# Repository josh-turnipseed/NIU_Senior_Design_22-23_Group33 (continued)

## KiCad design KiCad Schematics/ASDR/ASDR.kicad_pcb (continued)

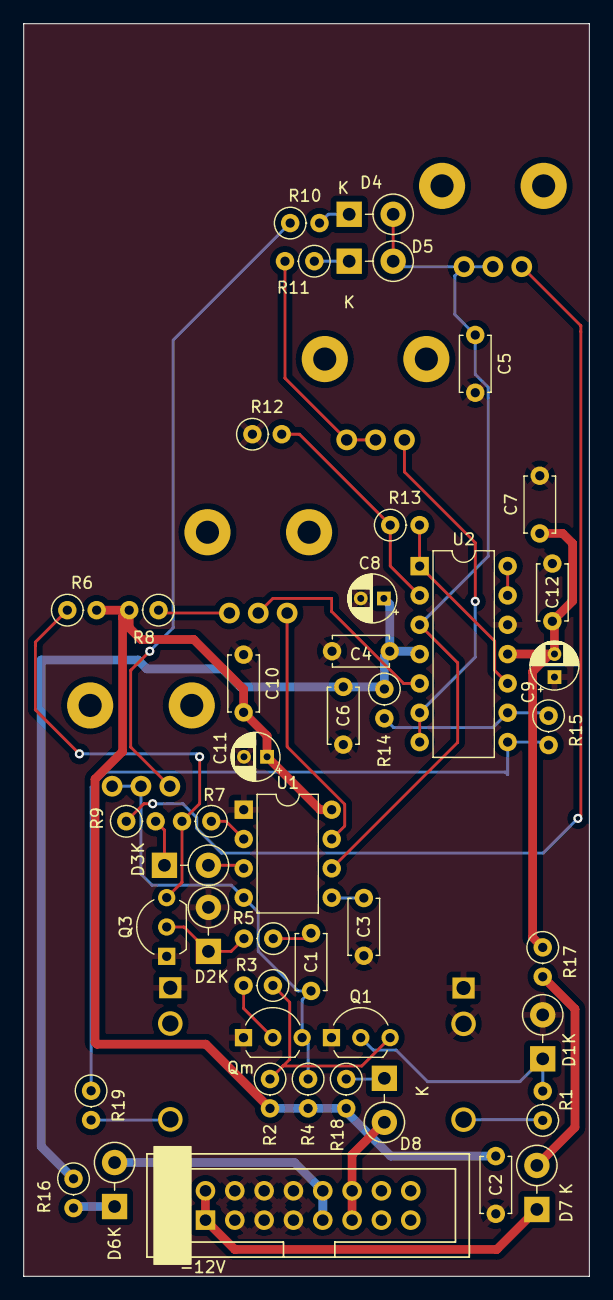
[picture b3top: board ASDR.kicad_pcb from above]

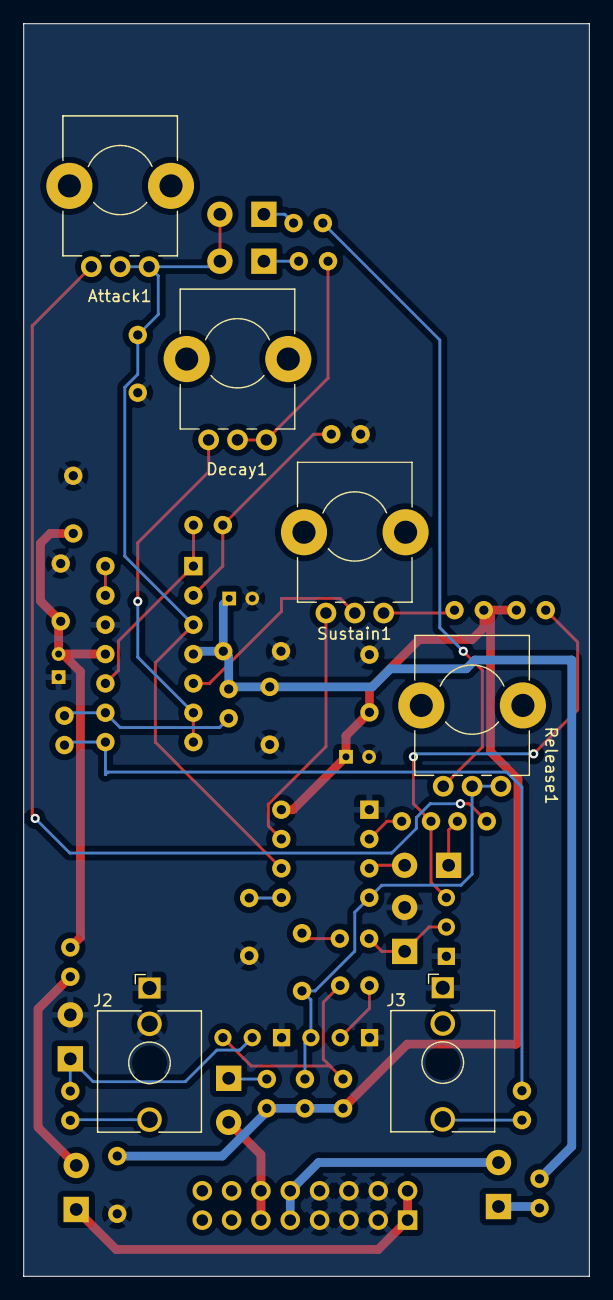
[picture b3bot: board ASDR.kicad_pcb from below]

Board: 2 copper layers, 49.0 x 108.5 mm, 51 parts (6 on the bottom side), 38 nets.

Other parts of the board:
Qm: 2N3904; TO-92L_Inline_Wide

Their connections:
GND: Qm.1 (E); also elsewhere on the board
unnamed 6: Qm.3 (C); also elsewhere on the board
unnamed 26: Qm.2 (B); also elsewhere on the board

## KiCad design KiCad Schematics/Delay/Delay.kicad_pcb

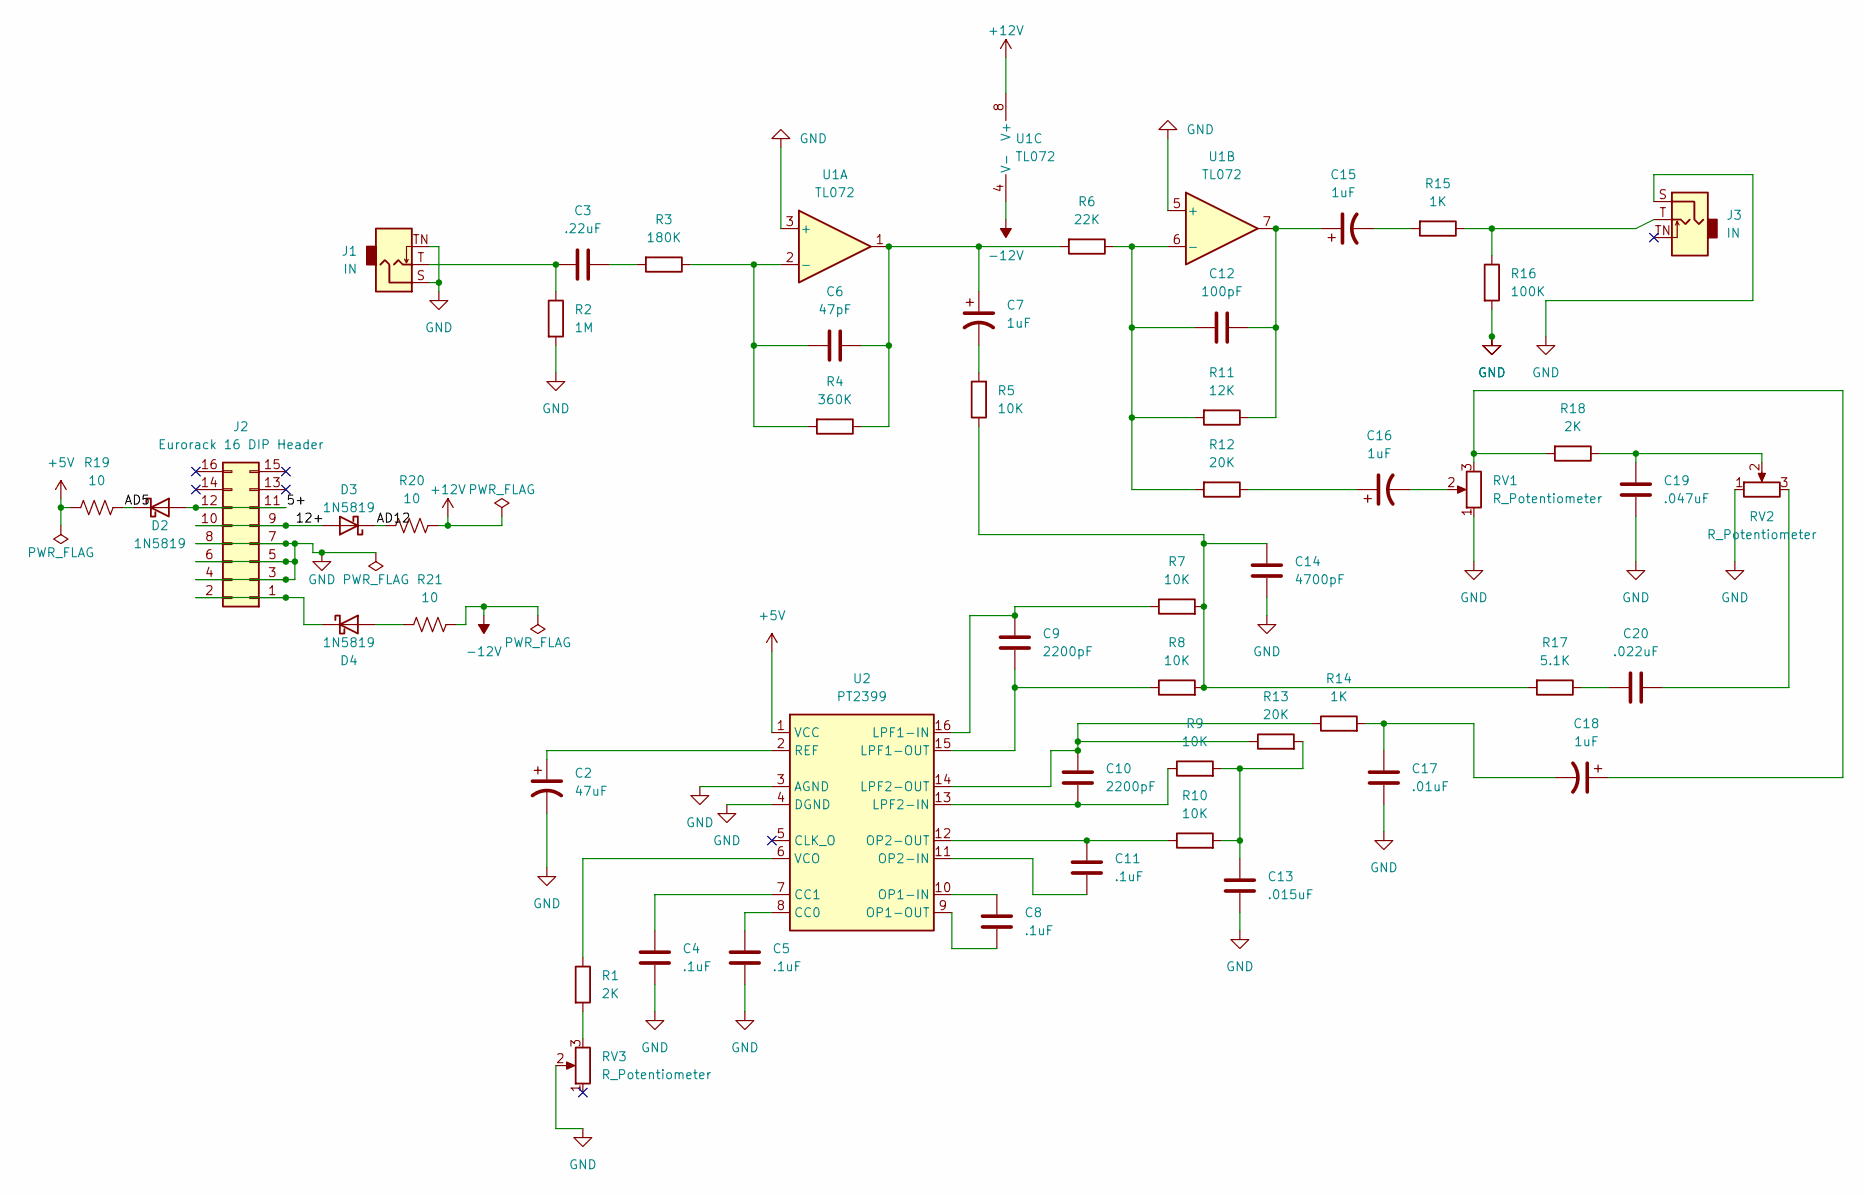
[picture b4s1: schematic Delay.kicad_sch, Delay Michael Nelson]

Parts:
C2: 47uF; CP_Radial_D5.0mm_P2.00mm
C3: .22uF; C_Disc_D3.8mm_W2.6mm_P2.50mm
C4, C5, C8, C11: .1uF; C_Disc_D3.8mm_W2.6mm_P2.50mm
C6: 47pF; C_Disc_D3.8mm_W2.6mm_P2.50mm
C7, C15, C16, C18: 1uF; CP_Radial_D5.0mm_P2.00mm
C9, C10: 2200pF; C_Disc_D3.8mm_W2.6mm_P2.50mm
C12: 100pF; C_Disc_D3.8mm_W2.6mm_P2.50mm
C13: .015uF; C_Disc_D3.8mm_W2.6mm_P2.50mm
C14: 4700pF; C_Disc_D3.8mm_W2.6mm_P2.50mm
C17: .01uF; C_Disc_D3.8mm_W2.6mm_P2.50mm
C19: .047uF; C_Disc_D3.8mm_W2.6mm_P2.50mm
C20: .022uF; C_Disc_D3.8mm_W2.6mm_P2.50mm
D2, D3, D4: 1N5819; D_DO-41_SOD81_P10.16mm_Horizontal
J1, J3: IN; Jack_3.5mm_QingPu_WQP-PJ398SM_Vertical_CircularHoles
J2: Eurorack 16 DIP Header; Eurorack_16_pin_header
R1, R18: 2K; R_Axial_DIN0207_L6.3mm_D2.5mm_P7.62mm_Horizontal
R2: 1M; R_Axial_DIN0207_L6.3mm_D2.5mm_P7.62mm_Horizontal
R3: 180K; R_Axial_DIN0207_L6.3mm_D2.5mm_P7.62mm_Horizontal
R4: 360K; R_Axial_DIN0207_L6.3mm_D2.5mm_P7.62mm_Horizontal
R5, R7, R8, R9, R10: 10K; R_Axial_DIN0207_L6.3mm_D2.5mm_P7.62mm_Horizontal
R6: 22K; R_Axial_DIN0207_L6.3mm_D2.5mm_P7.62mm_Horizontal
R11: 12K; R_Axial_DIN0207_L6.3mm_D2.5mm_P7.62mm_Horizontal
R12, R13: 20K; R_Axial_DIN0207_L6.3mm_D2.5mm_P7.62mm_Horizontal
R14, R15: 1K; R_Axial_DIN0207_L6.3mm_D2.5mm_P7.62mm_Horizontal
R16: 100K; R_Axial_DIN0207_L6.3mm_D2.5mm_P7.62mm_Horizontal
R17: 5.1K; R_Axial_DIN0207_L6.3mm_D2.5mm_P7.62mm_Horizontal
R19, R20, R21: 10; R_Axial_DIN0207_L6.3mm_D2.5mm_P7.62mm_Horizontal
RV1, RV2, RV3: R_Potentiometer; Alpha_9mm_Potentiometer
U1: TL072; DIP-8_W7.62mm
U2: PT2399; DIP-16_W7.62mm

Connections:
+5V: R19.2, U2.1 (VCC)
+12V: R20.1, U1.8 (V+)
-12V: R21.1, U1.4 (V-)
/5+: D2.2 (A), J2.11, J2.12
/12+: D3.2 (A), J2.9, J2.10
/AD5: D2.1 (K), R19.1
/AD12: D3.1 (K), R20.2
GND: C2.2, C4.2, C5.2, C13.2, C14.2, C17.2, C19.1, J1.S, J1.TN, J2.3, J2.4, J2.5, J2.6, J2.7, J2.8, J3.S, R2.2, R16.2, RV1.1, RV2.1, RV3.2, U1.3 (+), U1.5 (+), U2.3 (AGND), U2.4 (DGND)
unnamed: C2.1, U2.2 (REF)
unnamed: C3.1, J1.T, R2.1
unnamed: C3.2, R3.2
unnamed: C4.1, U2.7 (CC1)
unnamed: C5.1, U2.8 (CC0)
unnamed: C6.1, R3.1, R4.2, U1.2 (-)
unnamed: C6.2, C7.1, R4.1, R6.2, U1.1
unnamed: C7.2, R5.2
unnamed: C8.1, U2.10 (OP1-IN)
unnamed: C8.2, U2.9 (OP1-OUT)
unnamed: C9.1, R7.1, U2.16 (LPF1-IN)
unnamed: C9.2, R8.1, U2.15 (LPF1-OUT)
unnamed: C10.1, R13.1, R14.1, U2.14 (LPF2-OUT)
unnamed: C10.2, R9.1, U2.13 (LPF2-IN)
unnamed: C11.1, R10.1, U2.12 (OP2-OUT)
unnamed: C11.2, U2.11 (OP2-IN)
unnamed: C12.1, R6.1, R11.2, R12.2, U1.6 (-)
unnamed: C12.2, C15.1, R11.1, U1.7
unnamed: C13.1, R9.2, R10.2, R13.2
unnamed: C14.1, R5.1, R7.2, R8.2, R17.2
unnamed: C15.2, R15.2
unnamed: C16.1, R12.1
unnamed: C16.2, RV1.2
unnamed: C17.1, C18.2, R14.2
unnamed: C18.1, R18.2, RV1.3
unnamed: C19.2, R18.1, RV2.2
unnamed: C20.1, RV2.3
unnamed: C20.2, R17.1
unnamed: D4.1 (K), J2.1, J2.2
unnamed: D4.2 (A), R21.2
unnamed: J3.T, R15.1, R16.1
unnamed: R1.1, U2.6 (VCO)
unnamed: R1.2, RV3.3

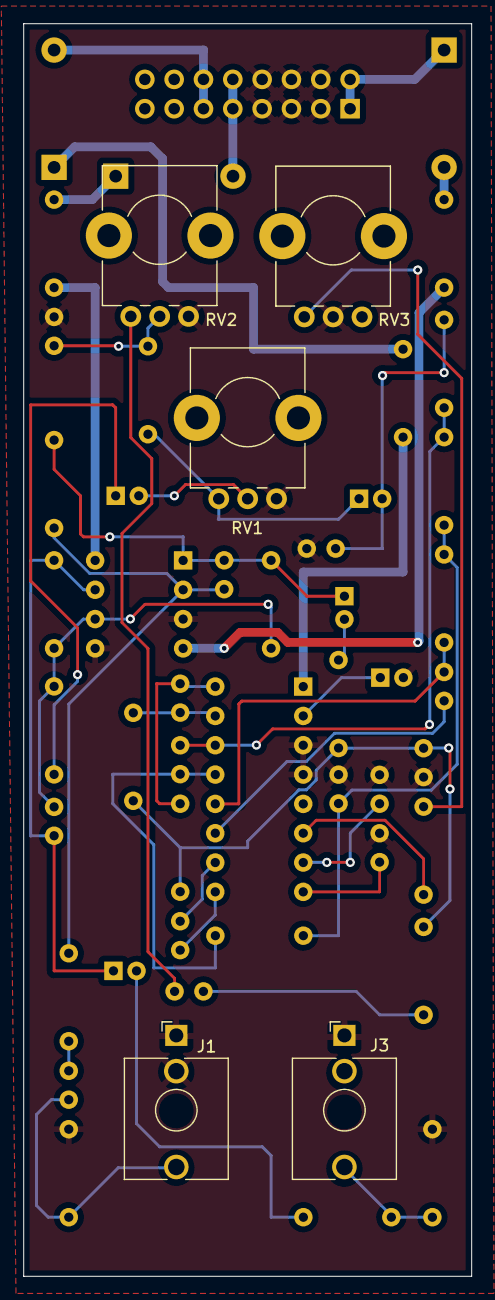
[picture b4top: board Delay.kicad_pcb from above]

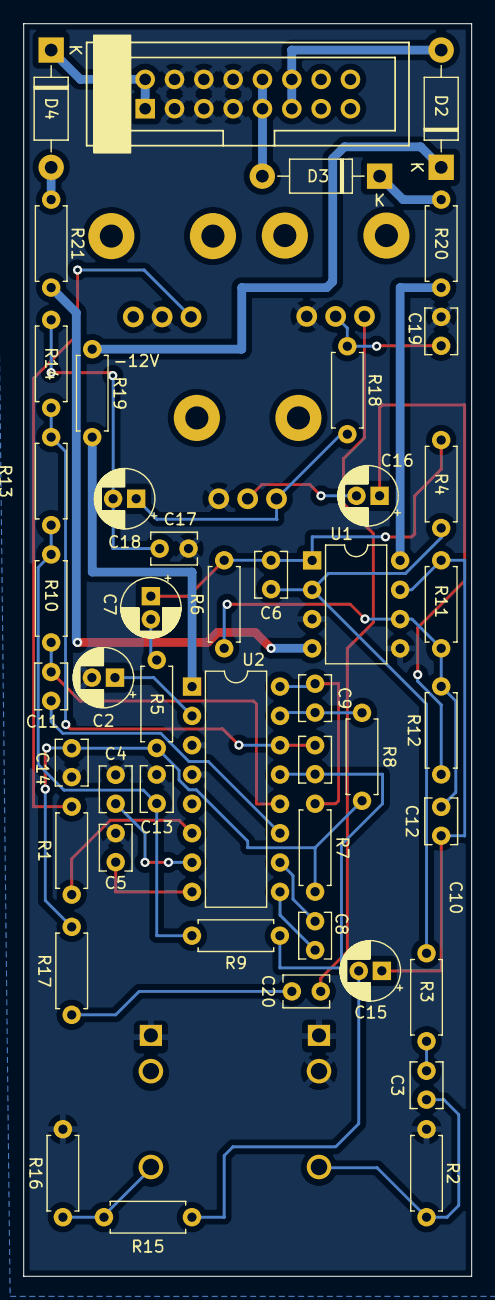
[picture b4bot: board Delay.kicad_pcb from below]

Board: 2 copper layers, 38.8 x 108.5 mm, 51 parts (46 on the bottom side), 41 nets.

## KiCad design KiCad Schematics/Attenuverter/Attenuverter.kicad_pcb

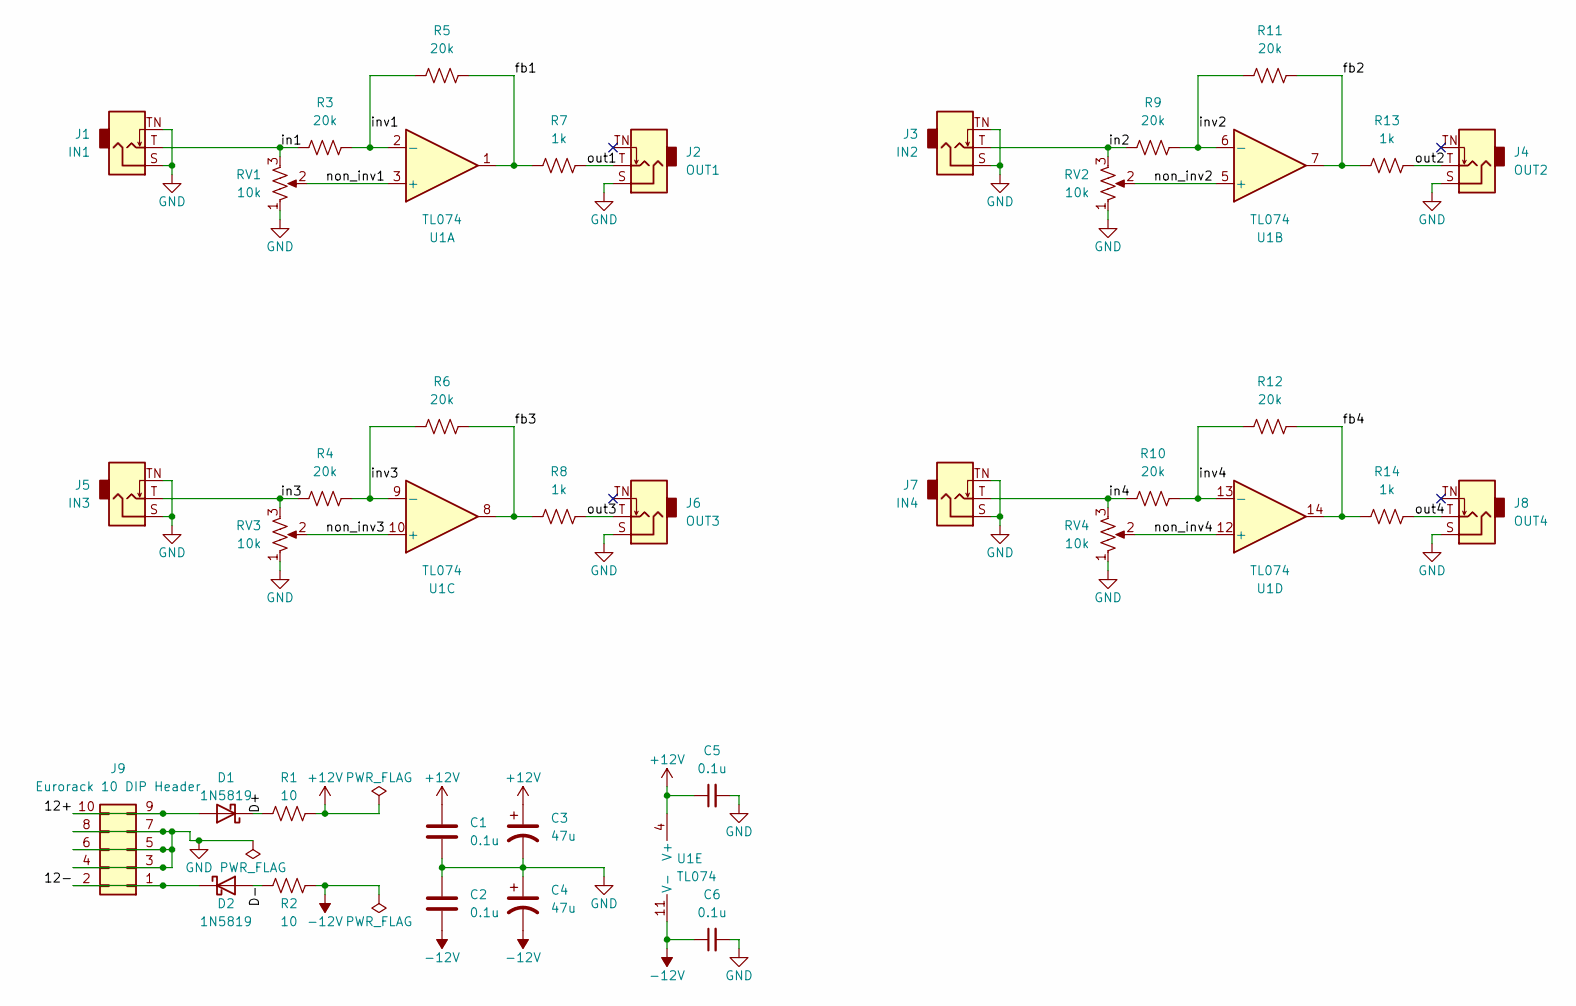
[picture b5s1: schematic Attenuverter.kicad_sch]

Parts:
C1, C2, C5, C6: 0.1u; C_Disc_D4.7mm_W2.5mm_P5.00mm
C3, C4: 47u; CP_Radial_D4.0mm_P2.00mm
D1, D2: 1N5819; D_DO-41_SOD81_P3.81mm_Vertical_KathodeUp
J1: IN1; Jack_3.5mm_QingPu_WQP-PJ398SM_Vertical_CircularHoles
J2: OUT1; Jack_3.5mm_QingPu_WQP-PJ398SM_Vertical_CircularHoles
J3: IN2; Jack_3.5mm_QingPu_WQP-PJ398SM_Vertical_CircularHoles
J4: OUT2; Jack_3.5mm_QingPu_WQP-PJ398SM_Vertical_CircularHoles
J5: IN3; Jack_3.5mm_QingPu_WQP-PJ398SM_Vertical_CircularHoles
J6: OUT3; Jack_3.5mm_QingPu_WQP-PJ398SM_Vertical_CircularHoles
J7: IN4; Jack_3.5mm_QingPu_WQP-PJ398SM_Vertical_CircularHoles
J8: OUT4; Jack_3.5mm_QingPu_WQP-PJ398SM_Vertical_CircularHoles
J9: Eurorack 10 DIP Header; Eurorack_10_pin_header
R1, R2: 10; R_Axial_DIN0207_L6.3mm_D2.5mm_P2.54mm_Vertical
R3, R4, R5, R6, R9, R10, R11, R12: 20k; R_Axial_DIN0207_L6.3mm_D2.5mm_P2.54mm_Vertical
R7, R8, R13, R14: 1k; R_Axial_DIN0207_L6.3mm_D2.5mm_P2.54mm_Vertical
RV1, RV2, RV3, RV4: 10k; Alpha_9mm_Potentiometer_Aligned
U1: TL074; DIP-14_W7.62mm

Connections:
+12V: C1.2, C3.1, C5.1, R1.1, U1.4 (V+)
-12V: C2.1, C4.2, C6.1, R2.1, U1.11 (V-)
/12+: D1.2 (A), J9.9, J9.10
/12-: D2.1 (K), J9.1, J9.2
/D+: D1.1 (K), R1.2
/D-: D2.2 (A), R2.2
/fb1: R5.2, R7.1, U1.1
/fb2: R11.2, R13.1, U1.7
/fb3: R6.2, R8.1, U1.8
/fb4: R12.2, R14.1, U1.14
/in1: J1.T, R3.1, RV1.3
/in2: J3.T, R9.1, RV2.3
/in3: J5.T, R4.1, RV3.3
/in4: J7.T, R10.1, RV4.3
/inv1: R3.2, R5.1, U1.2 (-)
/inv2: R9.2, R11.1, U1.6 (-)
/inv3: R4.2, R6.1, U1.9 (-)
/inv4: R10.2, R12.1, U1.13 (-)
/non_inv1: RV1.2, U1.3 (+)
/non_inv2: RV2.2, U1.5 (+)
/non_inv3: RV3.2, U1.10 (+)
/non_inv4: RV4.2, U1.12 (+)
/out1: J2.T, R7.2
/out2: J4.T, R13.2
/out3: J6.T, R8.2
/out4: J8.T, R14.2
GND: C1.1, C2.2, C3.2, C4.1, C5.2, C6.2, J1.S, J1.TN, J2.S, J3.S, J3.TN, J4.S, J5.S, J5.TN, J6.S, J7.S, J7.TN, J8.S, J9.3, J9.4, J9.5, J9.6, J9.7, J9.8, RV1.1, RV2.1, RV3.1, RV4.1

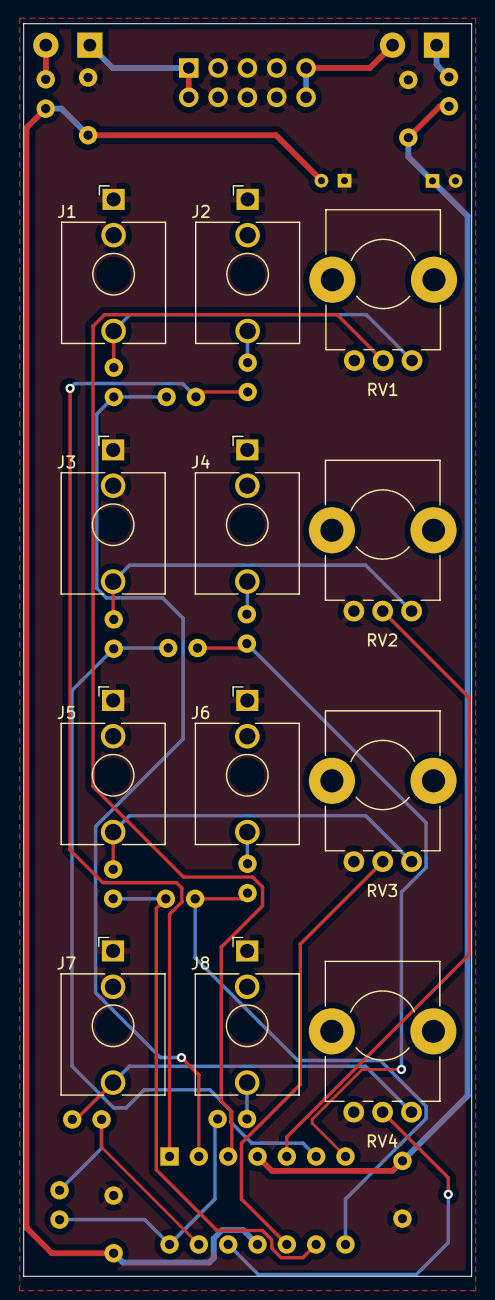
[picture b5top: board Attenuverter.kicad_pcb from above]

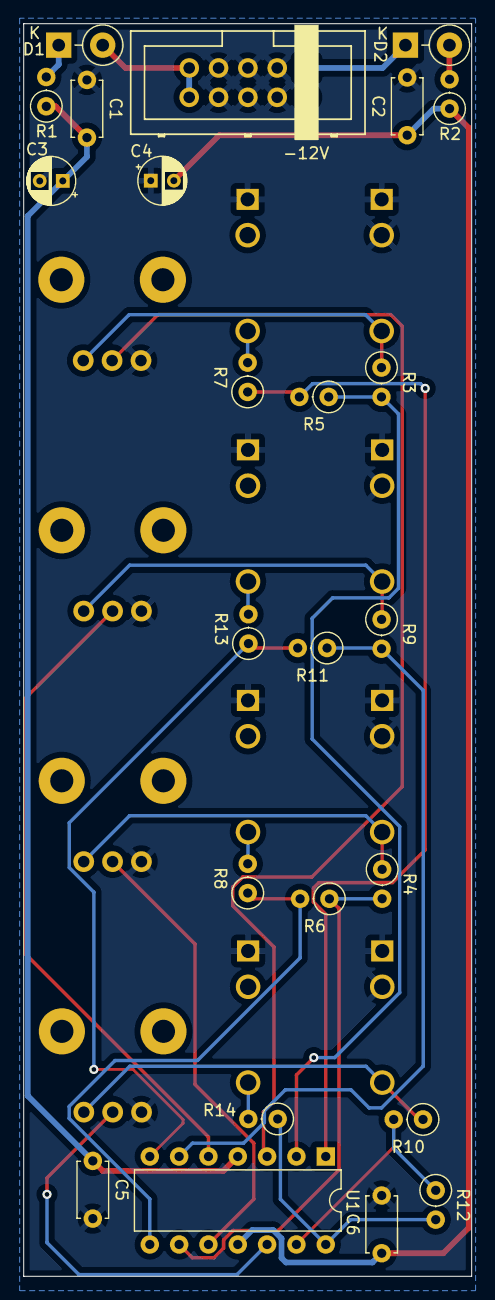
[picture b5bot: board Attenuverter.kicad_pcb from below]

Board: 2 copper layers, 38.8 x 108.5 mm, 36 parts (24 on the bottom side), 27 nets.

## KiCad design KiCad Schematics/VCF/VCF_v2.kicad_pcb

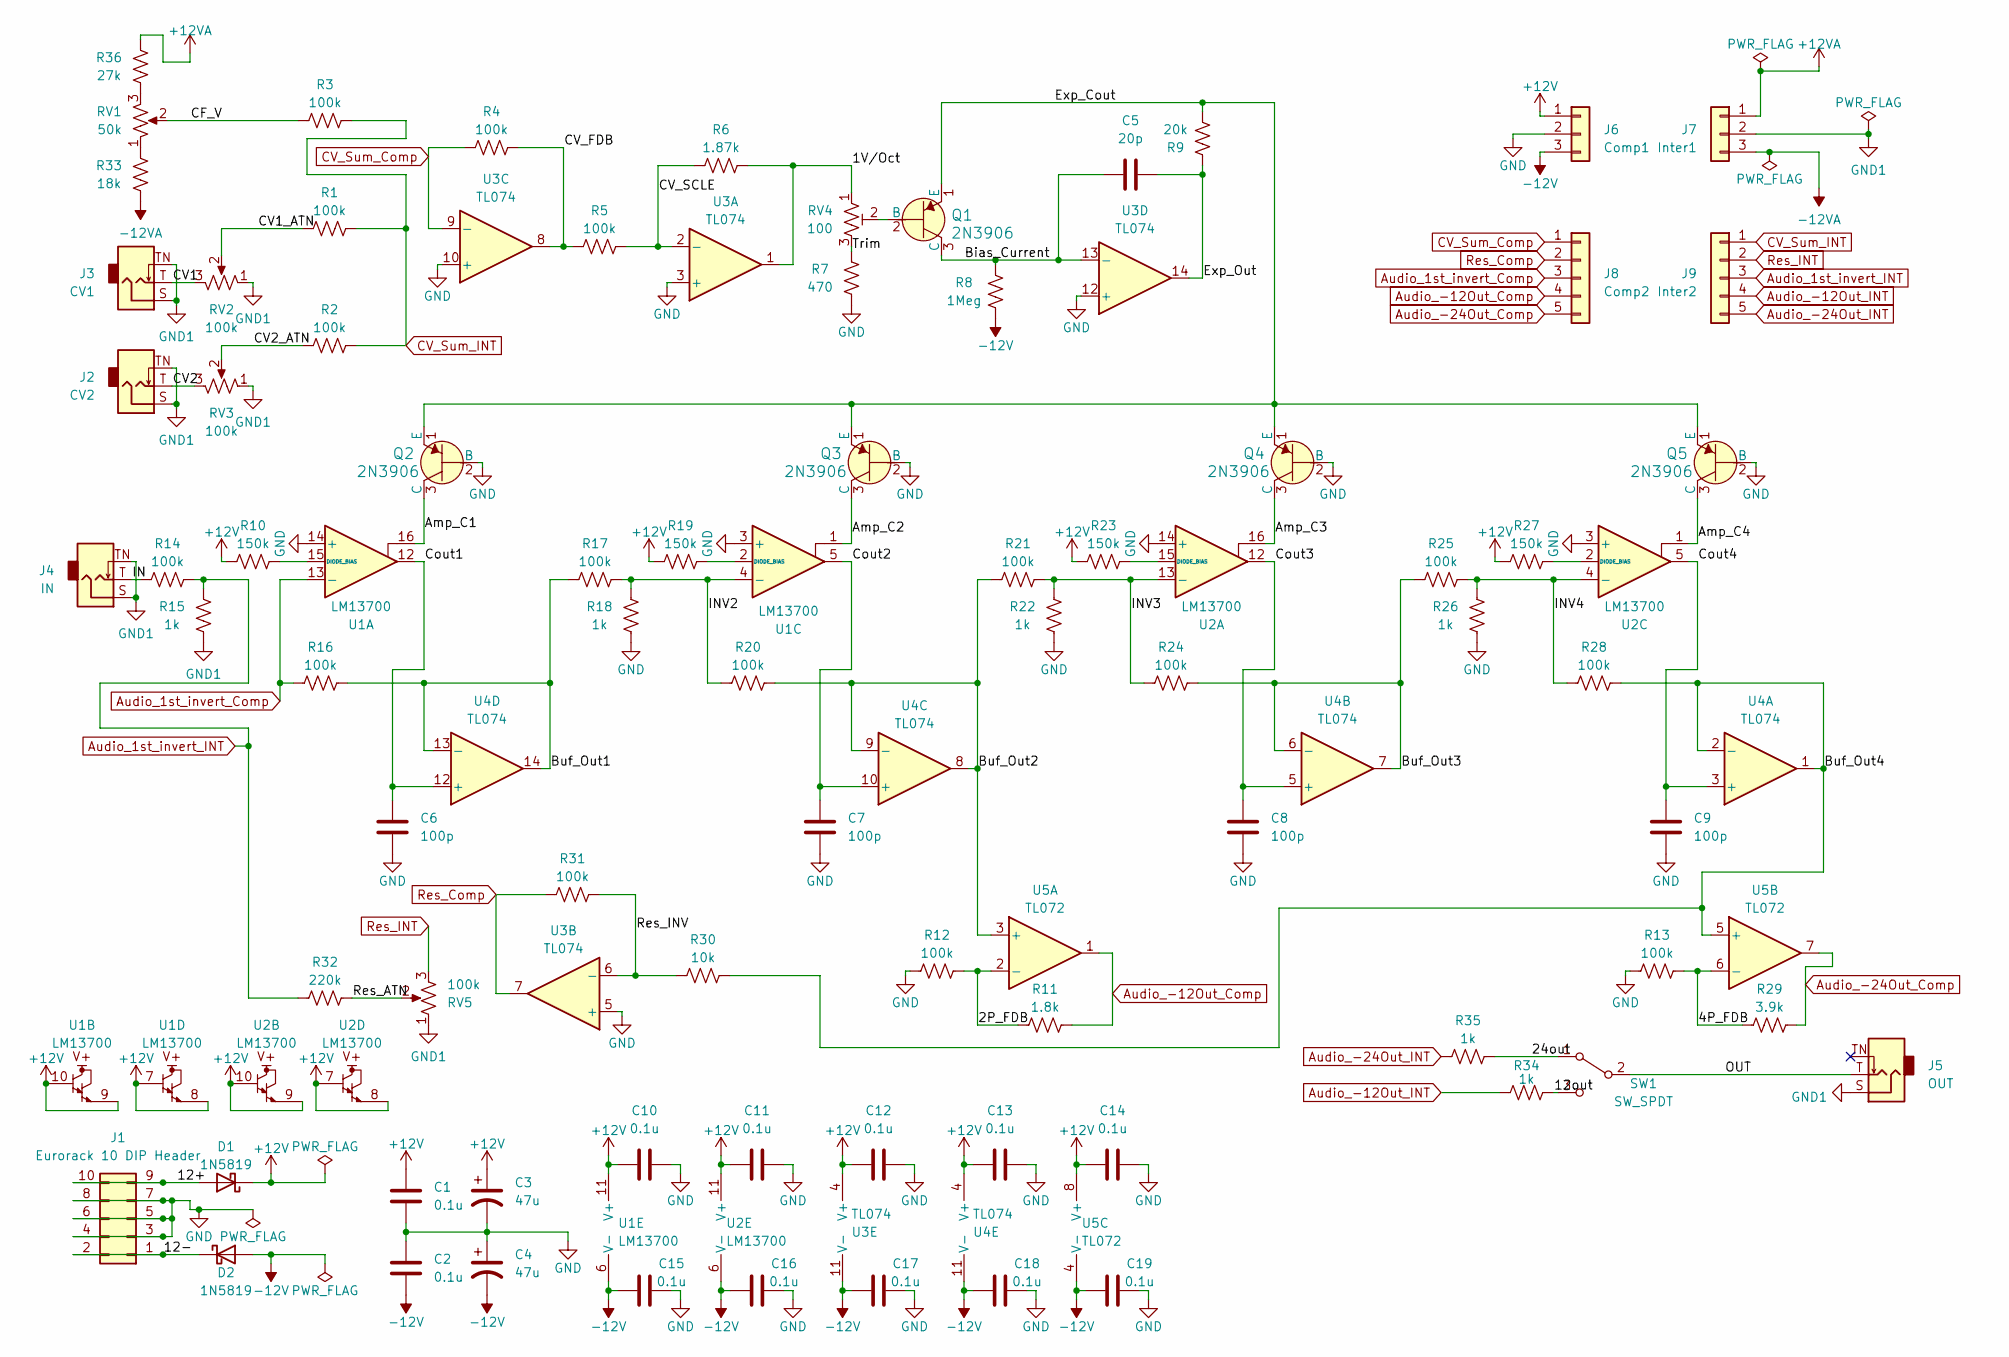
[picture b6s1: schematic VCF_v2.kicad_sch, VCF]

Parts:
C1, C2, C10, C11, C12, C13, C14, C15, C16, C17, C18, C19: 0.1u; C_Disc_D4.7mm_W2.5mm_P5.00mm
C3, C4: 47u; CP_Radial_D4.0mm_P2.00mm
C5: 20p; C_Disc_D4.7mm_W2.5mm_P5.00mm
C6, C7, C8, C9: 100p; C_Disc_D4.7mm_W2.5mm_P5.00mm
D1, D2: 1N5819; D_DO-41_SOD81_P3.81mm_Vertical_KathodeUp
J1: Eurorack 10 DIP Header; Eurorack_10_pin_header
J2: CV2; Jack_3.5mm_QingPu_WQP-PJ398SM_Vertical_CircularHoles
J3: CV1; Jack_3.5mm_QingPu_WQP-PJ398SM_Vertical_CircularHoles
J4: IN; Jack_3.5mm_QingPu_WQP-PJ398SM_Vertical_CircularHoles
J5: OUT; Jack_3.5mm_QingPu_WQP-PJ398SM_Vertical_CircularHoles
J6: Comp1; PinSocket_1x03_P2.54mm_Vertical
J7: Inter1; PinSocket_1x03_P2.54mm_Vertical
J8: Comp2; PinSocket_1x05_P2.54mm_Vertical
J9: Inter2; PinSocket_1x05_P2.54mm_Vertical
Q1, Q2, Q3, Q4, Q5: 2N3906; TO-92L_Inline_Wide; MPN 2N3906; Digi-Key_PN 2N3906CS-ND
R1, R2, R3, R14: 100k; R_Axial_DIN0204_L3.6mm_D1.6mm_P5.08mm_Horizontal
R4, R5, R12, R13, R16, R17, R20, R21, R24, R25, R28, R31: 100k; R_Axial_DIN0204_L3.6mm_D1.6mm_P2.54mm_Vertical
R6: 1.87k; R_Axial_DIN0204_L3.6mm_D1.6mm_P2.54mm_Vertical
R7: 470; R_Axial_DIN0204_L3.6mm_D1.6mm_P2.54mm_Vertical
R8: 1Meg; R_Axial_DIN0204_L3.6mm_D1.6mm_P2.54mm_Vertical
R9: 20k; R_Axial_DIN0204_L3.6mm_D1.6mm_P2.54mm_Vertical
R10, R19, R23, R27: 150k; R_Axial_DIN0204_L3.6mm_D1.6mm_P2.54mm_Vertical
R11: 1.8k; R_Axial_DIN0204_L3.6mm_D1.6mm_P2.54mm_Vertical
R15, R34, R35: 1k; R_Axial_DIN0204_L3.6mm_D1.6mm_P5.08mm_Horizontal
R18, R22, R26: 1k; R_Axial_DIN0204_L3.6mm_D1.6mm_P2.54mm_Vertical
R29: 3.9k; R_Axial_DIN0204_L3.6mm_D1.6mm_P2.54mm_Vertical
R30: 10k; R_Axial_DIN0204_L3.6mm_D1.6mm_P2.54mm_Vertical
R32: 220k; R_Axial_DIN0204_L3.6mm_D1.6mm_P5.08mm_Horizontal
R33: 18k; R_Axial_DIN0204_L3.6mm_D1.6mm_P5.08mm_Horizontal
R36: 27k; R_Axial_DIN0204_L3.6mm_D1.6mm_P5.08mm_Horizontal
RV1: 50k; Alpha_9mm_Potentiometer_Aligned
RV2, RV3, RV5: 100k; Alpha_9mm_Potentiometer_Aligned
RV4: 100; Potentiometer_Bourns_3296Y_Vertical
SW1: SW_SPDT; SPDT toggle on-off-on
U1, U2: LM13700; DIP-16_W7.62mm
U3, U4: TL074; DIP-14_W7.62mm
U5: TL072; DIP-8_W7.62mm

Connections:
+12V: C1.2, C3.1, C10.2, C11.2, C12.2, C13.2, C14.2, D1.1 (K), J6.1, R10.1, R19.1, R23.1, R27.1, U1.7, U1.8, U1.9, U1.10, U1.11 (V+), U2.7, U2.8, U2.9, U2.10, U2.11 (V+), U3.4 (V+), U4.4 (V+), U5.8 (V+)
+12VA: J7.1, R36.2
-12V: C2.1, C4.2, C15.2, C16.2, C17.2, C18.2, C19.2, D2.2 (A), J6.3, R8.1, U1.6 (V-), U2.6 (V-), U3.11 (V-), U4.11 (V-), U5.4 (V-)
-12VA: J7.3, R33.1
/1V/Oct: R6.2, RV4.1, U3.1
/2P_FDB: R11.1, R12.2, U5.2 (-)
/4P_FDB: R13.2, R29.1, U5.6 (-)
/12+: D1.2 (A), J1.9, J1.10
/12-: D2.1 (K), J1.1, J1.2
/12out: R34.2, SW1.3 (C)
/24out: R35.2, SW1.1 (A)
/Amp_C1: Q2.3 (C), U1.16
/Amp_C2: Q3.3 (C), U1.1
/Amp_C3: Q4.3 (C), U2.16
/Amp_C4: Q5.3 (C), U2.1
/Bias_Current: C5.2, Q1.3 (C), R8.2, U3.13 (-)
/Buf_Out1: R16.2, R17.1, U4.13 (-), U4.14
/Buf_Out2: R20.2, R21.1, U4.8, U4.9 (-), U5.3 (+)
/Buf_Out3: R24.2, R25.1, U4.6 (-), U4.7
/Buf_Out4: R28.2, R30.2, U4.1, U4.2 (-), U5.5 (+)
/CF_V: R3.1, RV1.2
/CV1: J3.T, RV2.3
/CV1_ATN: R1.1, RV2.2
/CV2: J2.T, RV3.3
/CV2_ATN: R2.1, RV3.2
/CV_FDB: R4.2, R5.1, U3.8
/CV_SCLE: R5.2, R6.1, U3.2 (-)
/Cout1: C6.2, U1.12, U4.12 (+)
/Cout2: C7.2, U1.5, U4.10 (+)
/Cout3: C8.2, U2.12, U4.5 (+)
/Cout4: C9.2, U2.5, U4.3 (+)
/Exp_Cout: Q1.1 (E), Q2.1 (E), Q3.1 (E), Q4.1 (E), Q5.1 (E), R9.2
/Exp_Out: C5.1, R9.1, U3.14
/IN: J4.T, R14.1
/INV2: R17.2, R18.2, R20.1, U1.4 (-)
/INV3: R21.2, R22.2, R24.1, U2.13 (-)
/INV4: R25.2, R26.2, R28.1, U2.4 (-)
/OUT: J5.T, SW1.2 (B)
/Res_ATN: R32.2, RV5.2
/Res_INV: R30.1, R31.2, U3.6 (-)
/Trim: R7.2, RV4.3
Audio_1st_invert_Comp: J8.3, R16.1, U1.13 (-)
Audio_1st_invert_INT: J9.3, R14.2, R15.2, R32.1
Audio_-12Out_Comp: J8.4, R11.2, U5.1
Audio_-12Out_INT: J9.4, R34.1
Audio_-24Out_Comp: J8.5, R29.2, U5.7
Audio_-24Out_INT: J9.5, R35.1
CV_Sum_Comp: J8.1, R4.1, U3.9 (-)
CV_Sum_INT: J9.1, R1.2, R2.2, R3.2
GND: C1.1, C2.2, C3.2, C4.1, C6.1, C7.1, C8.1, C9.1, C10.1, C11.1, C12.1, C13.1, C14.1, C15.1, C16.1, C17.1, C18.1, C19.1, J1.3, J1.4, J1.5, J1.6, J1.7, J1.8, J6.2, Q2.2 (B), Q3.2 (B), Q4.2 (B), Q5.2 (B), R7.1, R12.1, R13.1, R18.1, R22.1, R26.1, U1.3 (+), U1.14 (+), U2.3 (+), U2.14 (+), U3.3 (+), U3.5 (+), U3.10 (+), U3.12 (+)
GND1: J2.S, J2.TN, J3.S, J3.TN, J4.S, J4.TN, J5.S, J7.2, R15.1, RV2.1, RV3.1, RV5.1
unnamed: Q1.2 (B), RV4.2
unnamed: R33.2, RV1.1
unnamed: R36.1, RV1.3
unnamed: R10.2, U1.15 (DIODE_BIAS)
unnamed: R19.2, U1.2 (DIODE_BIAS)
unnamed: R23.2, U2.15 (DIODE_BIAS)
unnamed: R27.2, U2.2 (DIODE_BIAS)
Res_Comp: J8.2, R31.1, U3.7
Res_INT: J9.2, RV5.3

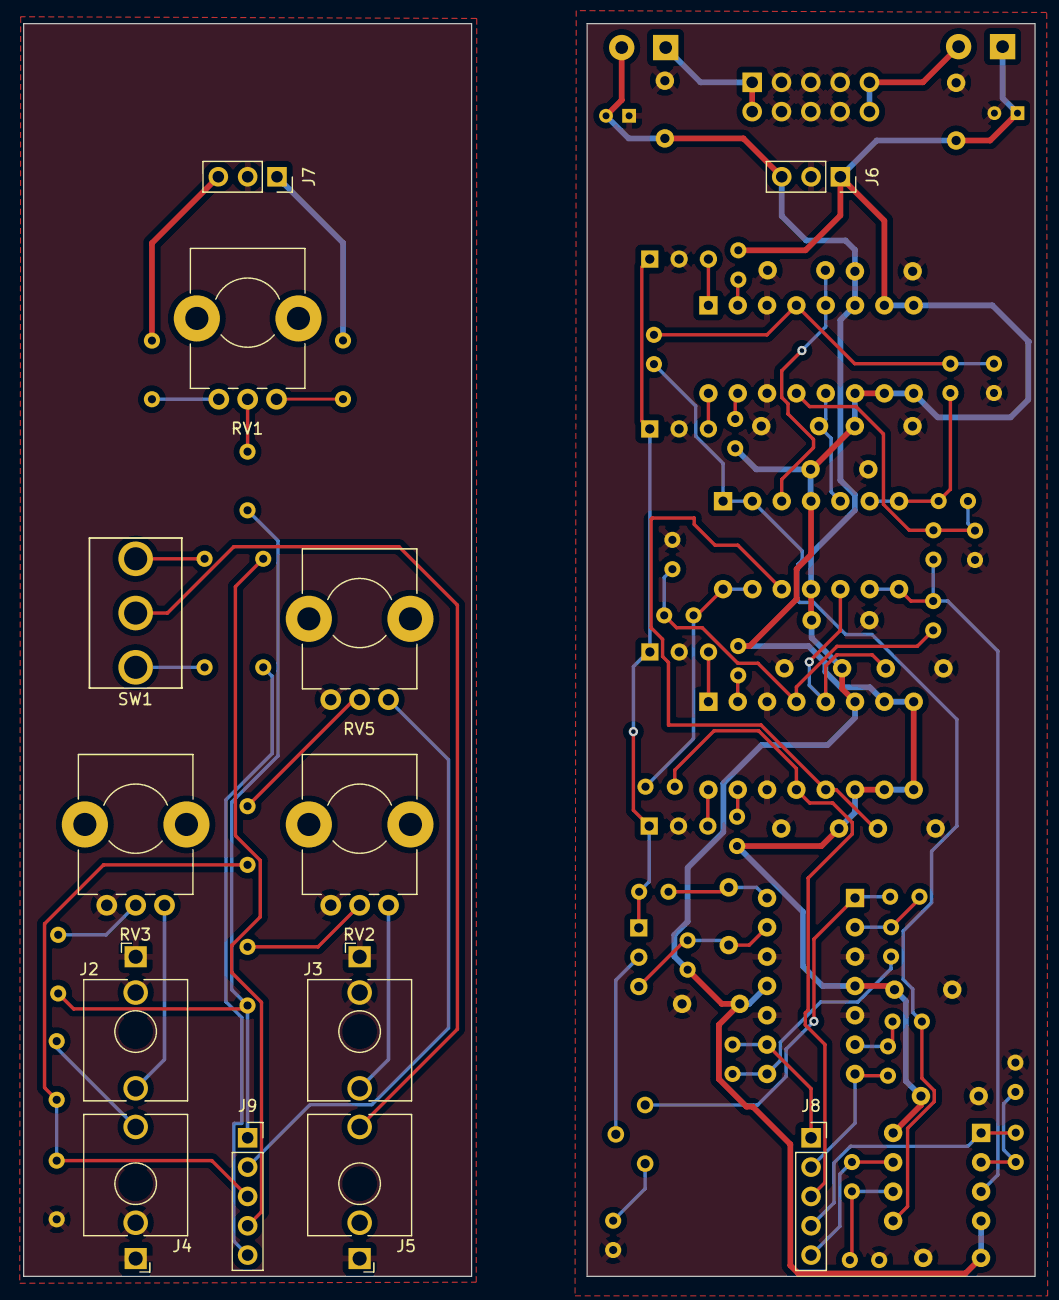
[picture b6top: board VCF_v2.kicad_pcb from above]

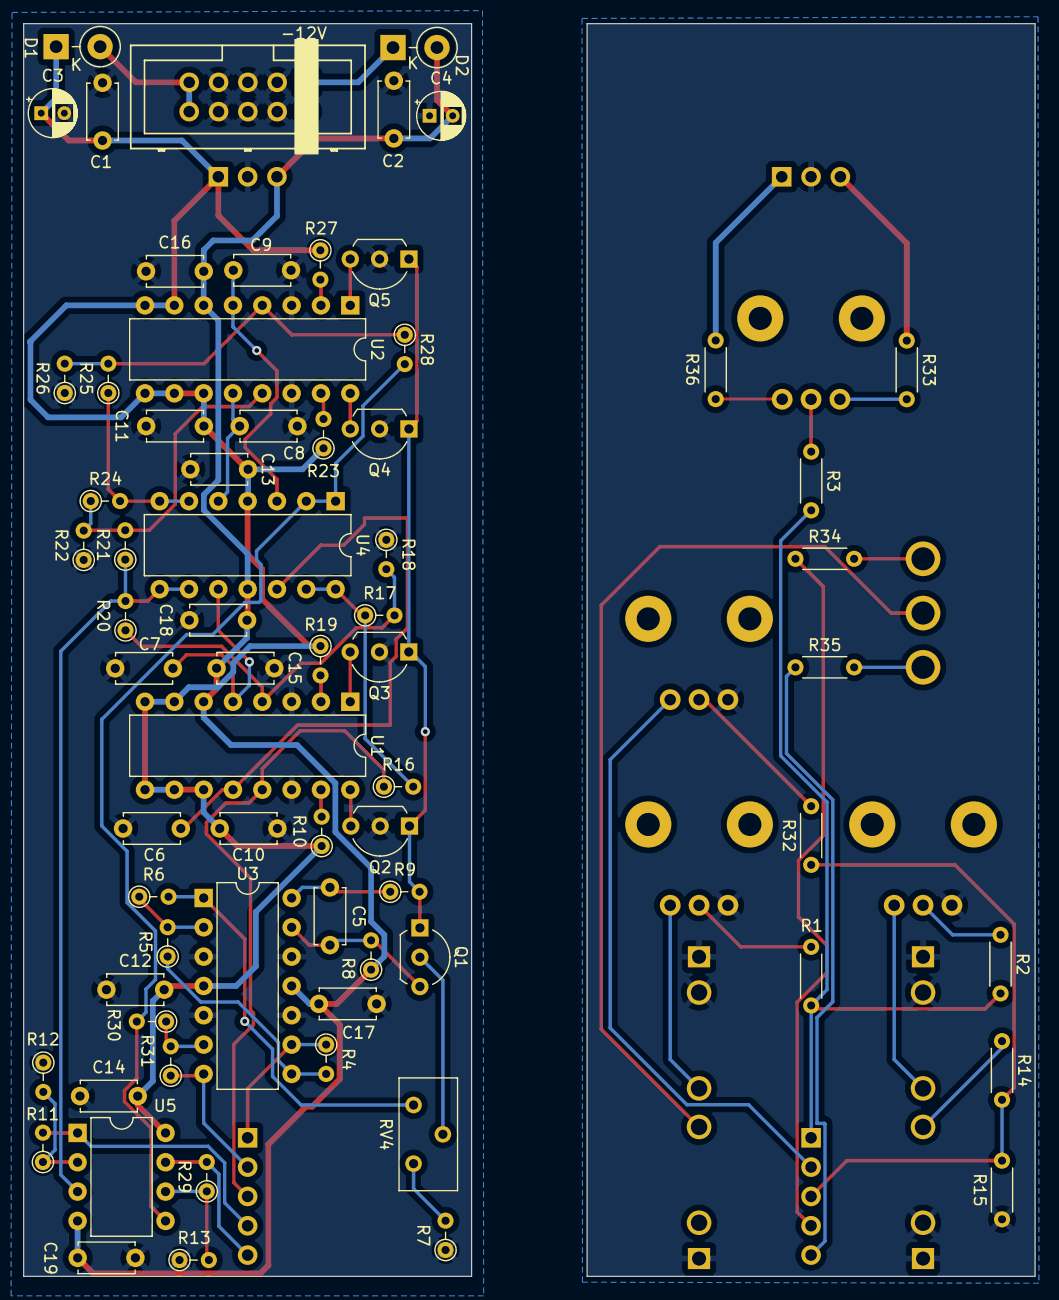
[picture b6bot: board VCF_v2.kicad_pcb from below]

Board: 2 copper layers, 87.6 x 108.5 mm, 82 parts (69 on the bottom side), 60 nets.
